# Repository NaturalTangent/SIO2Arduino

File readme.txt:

This is the fork of the battlecoder's code.
I've added the support for the Arduino Leonardo board.

Original readme:
------------------------------------------------------------------
This is a fork of Daniel Noguerol's SIO2Arduino Project.

I made the following modifications:
 * Added the SdFat library to the project folder. Apparently it requires an old version so -since the library is GPL- I've included it here. Copy the folder to your Arduino libraries path before compiling the sketch.
 * Added several forward declarations so the code compiles under recent versions of the Arduino IDE.
 * Moved the RESET button code to the setup function so it's only checked during the device startup.
 * Changed the behavior of the button so it doesn't trigger continuously while it's pressed.
 
With the changes above the optional automount feature can coexist peacefully with the image selection mechanism, so you get both options if you select them.

I also created a simple PCB to wire everything together in a more compact device.
You can find more information here: http://blog.damnsoft.org/custom-pcb-for-sio2arduino/

------------------------------------------------------------------
:: ORIGINAL README FOLLOWS ::
------------------------------------------------------------------
SIO2Arduino is an open-source implementation of the Atari SIO device protocol that runs on Arduino hardware. Arduino hardware is open-source and can be assembled by hand or purchased preassembled.

Note: You will need the SdFat library (http://code.google.com/p/sdfatlib/) in your Arduino libraries directory in order to compile.

For more information on SIO2Arduino, see the website at: 
http://www.whizzosoftware.com/sio2arduino

For more information on the Arduino platform, go to:
http://www.arduino.cc

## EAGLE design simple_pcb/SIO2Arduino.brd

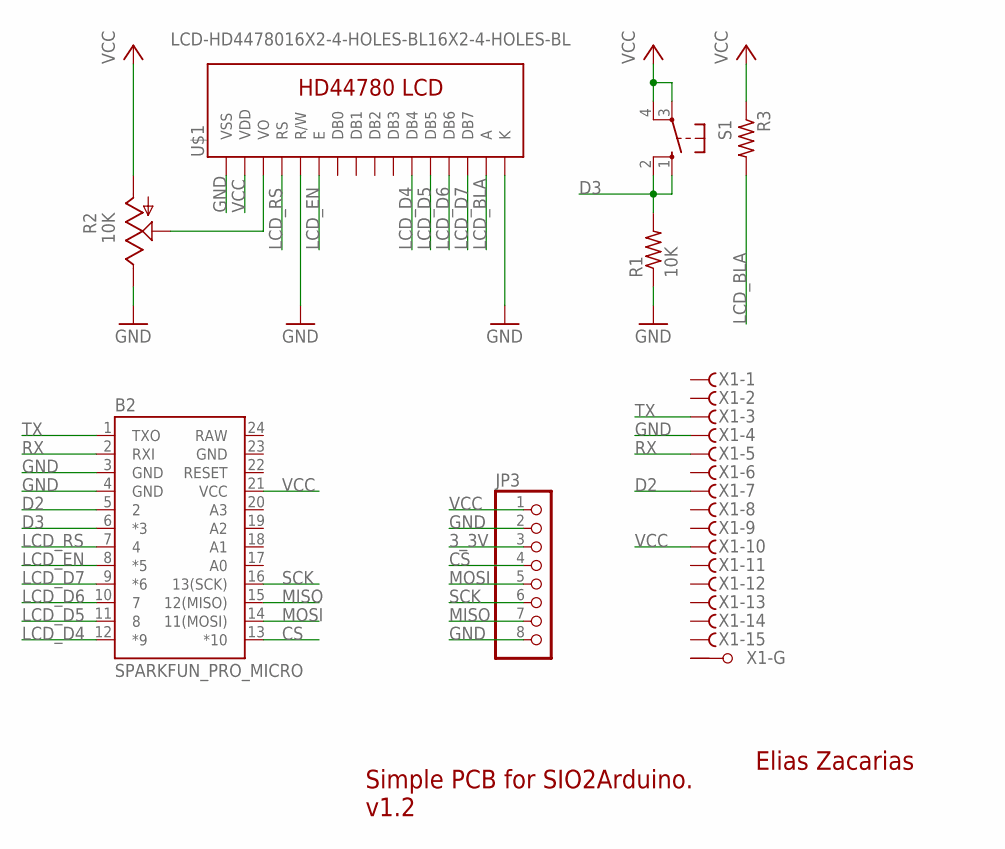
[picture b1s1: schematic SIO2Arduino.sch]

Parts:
B2: SPARKFUN_PRO_MICRO
JP3: PINHD-1X8; 1X08
R1: 10K; 0207/7
R2: 10K; CA6V
R3: R-US_0207/7; 0207/7
S1: 10-XX; B3F-10XX
U$1: LCD-HD4478016X2-4-HOLES-BL16X2-4-HOLES-BL; LCD-16X2-4HOLES-BL
X1: F15HPS; F15HP

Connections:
3_3V: JP3.3
CS: B2.13 (*10), JP3.4
D2: B2.5 (2), X1.7 (F)
D3: B2.6 (*3), R1.2, S1.1 (S), S1.2 (S1)
GND: B2.3 (GND), B2.4 (GND), B2.23 (GND), JP3.2, JP3.8, R1.1, R2.E, U$1.1 (VSS), U$1.5 (R/W), U$1.16 (K), X1.4 (F)
LCD_BLA: R3.2, U$1.15 (A)
LCD_D4: B2.12 (*9), U$1.11 (DB4)
LCD_D5: B2.11 (8), U$1.12 (DB5)
LCD_D6: B2.10 (7), U$1.13 (DB6)
LCD_D7: B2.9 (*6), U$1.14 (DB7)
LCD_EN: B2.8 (*5), U$1.6 (E)
LCD_RS: B2.7 (4), U$1.4 (RS)
MISO: B2.15 (12(MISO)), JP3.7
MOSI: B2.14 (11(MOSI)), JP3.5
unnamed: R2.S, U$1.3 (VO)
RAW: B2.24 (RAW)
RX: B2.2 (RXI), X1.5 (F)
SCK: B2.16 (13(SCK)), JP3.6
TX: B2.1 (TXO), X1.3 (F)
VCC: B2.21 (VCC), JP3.1, R2.A, R3.1, S1.3, S1.4 (P1), U$1.2 (VDD), X1.10 (F)

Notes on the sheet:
Elias Zacarias
Simple PCB for SIO2Arduino. v1.2

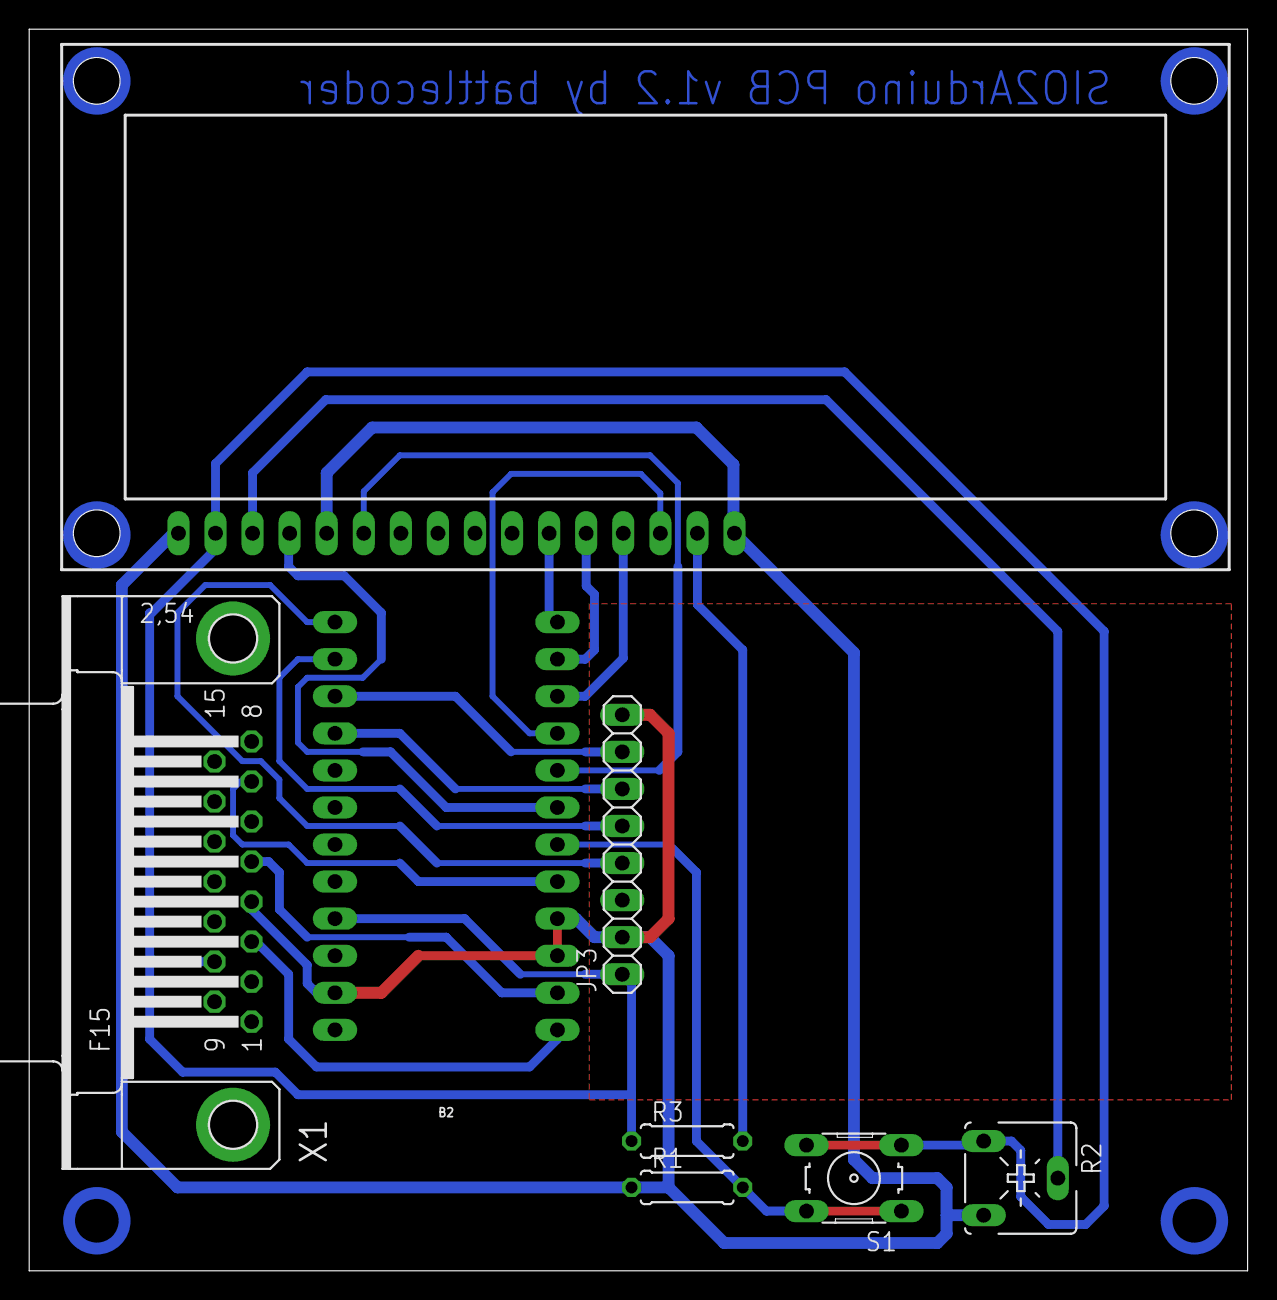
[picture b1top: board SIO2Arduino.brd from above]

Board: 2 copper layers, 83.5 x 85.1 mm, 8 parts (0 on the bottom side), 18 nets.

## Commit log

2017-01-03 Minor modifications
2017-01-03 Added the Custom PCB
2017-01-07 Updated PCB with version number. Fixed readme
2017-02-16 Added support for Arduino Leonardo
2017-02-26 Hacked in support for LCD Keypad shield on Arduino Mega. #define LCD_KEYPAD_SHEILD
    (note spelling error!)
2017-03-19 Change pin allocated to atari sio command from 46 to 17. Add newlines on debug output.

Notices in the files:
parts and their libraries:
SparkFun-Boards: Licensing: Creative Commons ShareAlike 4.0 International - https://creativecommons.org/licenses/by-sa/4.0
